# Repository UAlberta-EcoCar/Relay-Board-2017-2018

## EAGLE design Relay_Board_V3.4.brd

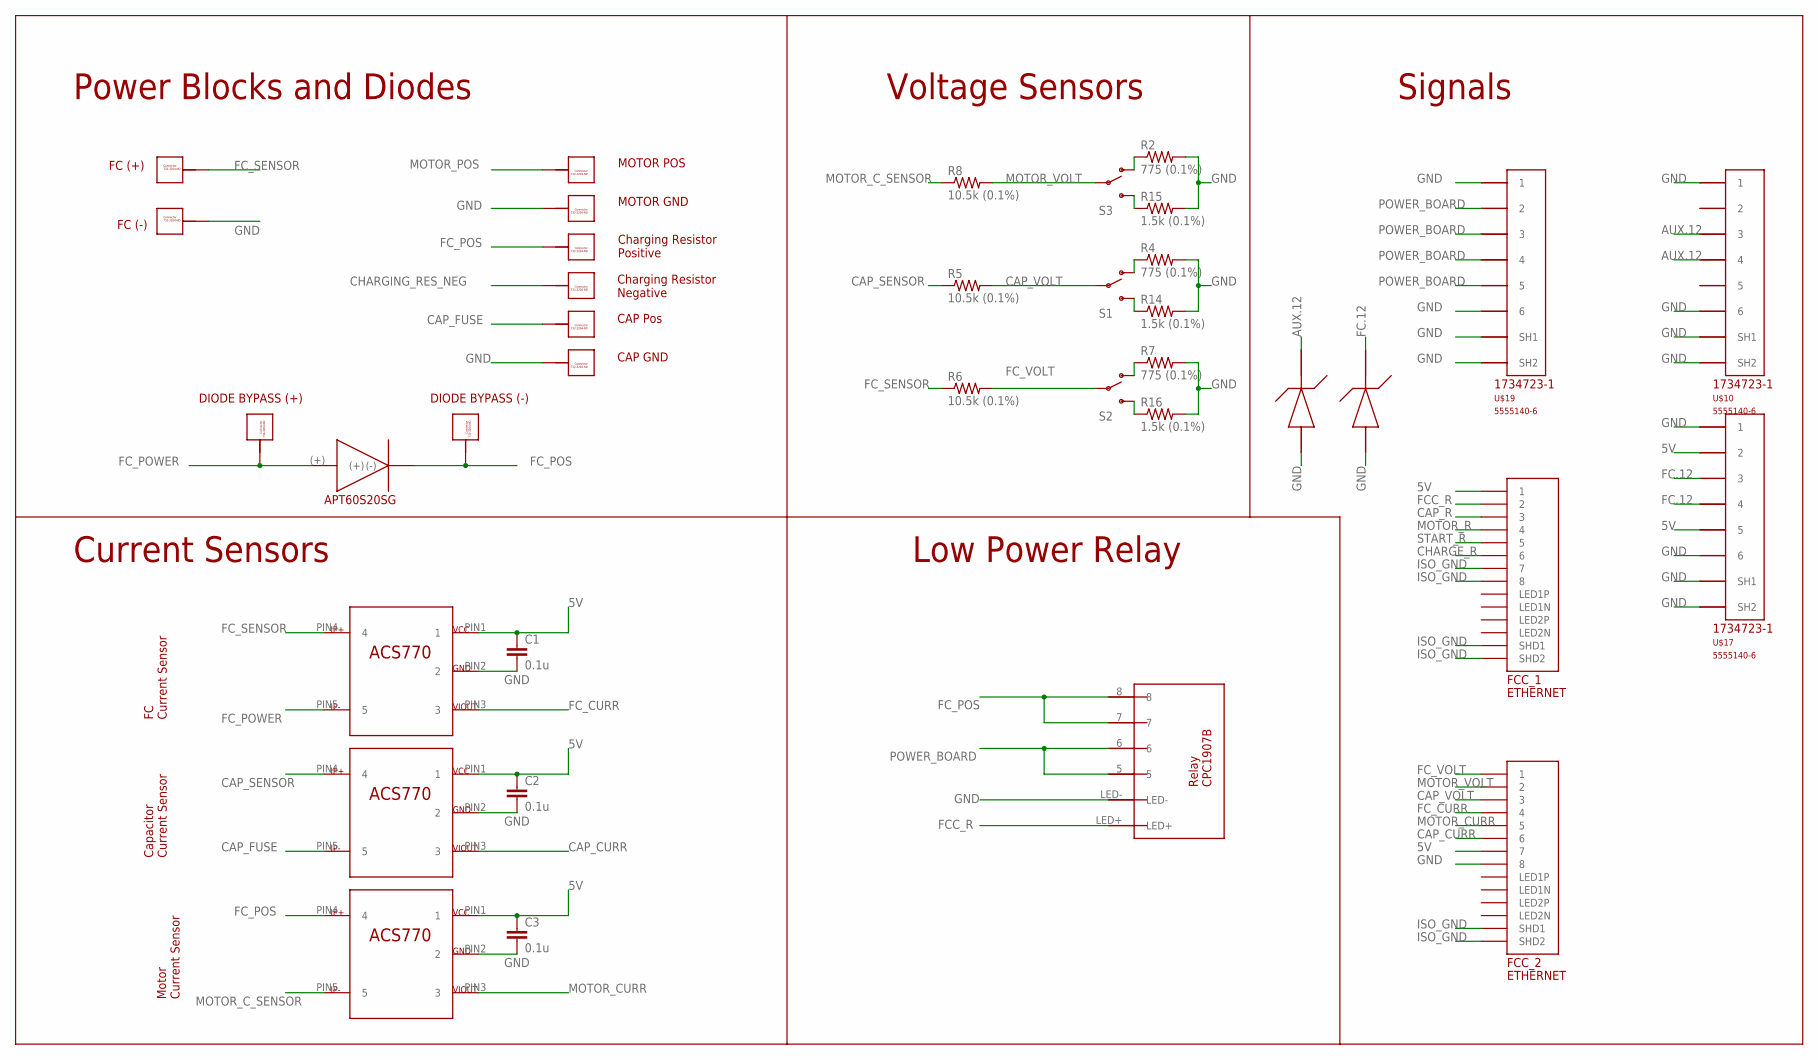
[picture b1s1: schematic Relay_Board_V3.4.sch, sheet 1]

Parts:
C1, C2, C3: 0.1u; 0603-CAP
CAP.GND, CAP.POS, CAP.POS1, CAP.POS2: 732-3204-ND_CONNECTOR; 732-3204-ND
D1: APT60S20SG; TO268
FC.GND, FC.POS: 732-3204-ND_CONNECTOR; 732-3204-ND
FCC_1, FCC_2: ETHERNET; A122645-ND
MOTOR.GROUND, MOTOR.POSITIVE: 732-3204-ND_CONNECTOR; 732-3204-ND
R2, R4, R7: 775 (0.1%); R0805
R5, R6, R8: 10.5k (0.1%); R0805
R14, R15, R16: 1.5k (0.1%); R0805
RES.NEG, RES.POS: 732-3204-ND_CONNECTOR; 732-3204-ND
S1, S2, S3: SWITCH-SPDTPTH; SWITCH-SPDT
U$7, U$8, U$9: ACS770LCB_CURRENTSENSOR
U$10, U$17, U$19: 5555140-6; 1734723-1_RJ11
U$15, U$16: P6KE15A-E3/54GICT-ND_TVS_DIODE
U$22: RELAY-CPC1907B

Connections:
5V: C1.1, C2.1, C3.1, FCC_1.P$1 (1), FCC_2.P$7 (7), U$7.PIN1 (1), U$8.PIN1 (1), U$9.PIN1 (1), U$17.2, U$17.5
AUX.12: U$10.3, U$10.4, U$16.P$2 (P(-)); also elsewhere on the board
CAP_CURR: FCC_2.P$6 (6), U$8.PIN3 (3)
CAP_FUSE: CAP.POS.P$1, CAP.POS.P$2, CAP.POS.P$3, CAP.POS.P$4, CAP.POS.P$5, CAP.POS.P$6, CAP.POS.P$7, CAP.POS.P$8, CAP.POS.P$9, CAP.POS.P$10, U$8.PIN5 (5)
CAP_R: FCC_1.P$3 (3); also elsewhere on the board
CAP_SENSOR: R5.1, U$8.PIN4 (4); also elsewhere on the board
CAP_VOLT: FCC_2.P$3 (3), R5.2, S1.2
CHARGE_R: FCC_1.P$6 (6); also elsewhere on the board
CHARGING_RES_NEG: RES.NEG.P$1, RES.NEG.P$2, RES.NEG.P$3, RES.NEG.P$4, RES.NEG.P$5, RES.NEG.P$6, RES.NEG.P$7, RES.NEG.P$8, RES.NEG.P$9, RES.NEG.P$10; also elsewhere on the board
FC.12: U$15.P$2 (P(-)), U$17.3, U$17.4; also elsewhere on the board
FCC_R: FCC_1.P$2 (2), U$22.LED+
FC_CURR: FCC_2.P$4 (4), U$7.PIN3 (3)
FC_POS: CAP.POS2.P$1, CAP.POS2.P$2, CAP.POS2.P$3, CAP.POS2.P$4, CAP.POS2.P$5, CAP.POS2.P$6, CAP.POS2.P$7, CAP.POS2.P$8, CAP.POS2.P$9, CAP.POS2.P$10, D1.(-), D1.C@1 ((-)), D1.C@2 ((-)), RES.POS.P$1, RES.POS.P$2, RES.POS.P$3, RES.POS.P$4, RES.POS.P$5, RES.POS.P$6, RES.POS.P$7, RES.POS.P$8, RES.POS.P$9, RES.POS.P$10, U$9.PIN4 (4), U$22.7, U$22.8; also elsewhere on the board
FC_POWER: CAP.POS1.P$1, CAP.POS1.P$2, CAP.POS1.P$3, CAP.POS1.P$4, CAP.POS1.P$5, CAP.POS1.P$6, CAP.POS1.P$7, CAP.POS1.P$8, CAP.POS1.P$9, CAP.POS1.P$10, D1.(+), U$7.PIN5 (5)
FC_SENSOR: FC.POS.P$1, FC.POS.P$2, FC.POS.P$3, FC.POS.P$4, FC.POS.P$5, FC.POS.P$6, FC.POS.P$7, FC.POS.P$8, FC.POS.P$9, FC.POS.P$10, R6.1, U$7.PIN4 (4)
FC_VOLT: FCC_2.P$1 (1), R6.2, S2.2
GND: C1.2, C2.2, C3.2, CAP.GND.P$1, CAP.GND.P$2, CAP.GND.P$3, CAP.GND.P$4, CAP.GND.P$5, CAP.GND.P$6, CAP.GND.P$7, CAP.GND.P$8, CAP.GND.P$9, CAP.GND.P$10, FC.GND.P$1, FC.GND.P$2, FC.GND.P$3, FC.GND.P$4, FC.GND.P$5, FC.GND.P$6, FC.GND.P$7, FC.GND.P$8, FC.GND.P$9, FC.GND.P$10, FCC_2.P$8 (8), MOTOR.GROUND.P$1, MOTOR.GROUND.P$2, MOTOR.GROUND.P$3, MOTOR.GROUND.P$4, MOTOR.GROUND.P$5, MOTOR.GROUND.P$6, MOTOR.GROUND.P$7, MOTOR.GROUND.P$8, MOTOR.GROUND.P$9, MOTOR.GROUND.P$10, R2.2, R4.2, R7.2, R14.2, R15.2, R16.2, U$7.PIN2 (2), U$8.PIN2 (2), U$9.PIN2 (2), U$10.1, U$10.6, U$10.SH1, U$10.SH2, U$15.P$1 (P(+)), U$16.P$1 (P(+)), U$17.1, U$17.6, U$17.SH1, U$17.SH2, U$19.1, U$19.6, U$19.SH1, U$19.SH2, U$22.LED-; also elsewhere on the board
ISO_GND: FCC_1.P$7 (7), FCC_1.P$8 (8), FCC_1.P$13 (SHD1), FCC_1.P$14 (SHD2), FCC_2.P$13 (SHD1), FCC_2.P$14 (SHD2); also elsewhere on the board
MOTOR_CURR: FCC_2.P$5 (5), U$9.PIN3 (3)
MOTOR_C_SENSOR: R8.1, U$9.PIN5 (5); also elsewhere on the board
MOTOR_POS: MOTOR.POSITIVE.P$1, MOTOR.POSITIVE.P$2, MOTOR.POSITIVE.P$3, MOTOR.POSITIVE.P$4, MOTOR.POSITIVE.P$5, MOTOR.POSITIVE.P$6, MOTOR.POSITIVE.P$7, MOTOR.POSITIVE.P$8, MOTOR.POSITIVE.P$9, MOTOR.POSITIVE.P$10; also elsewhere on the board
MOTOR_R: FCC_1.P$4 (4); also elsewhere on the board
MOTOR_VOLT: FCC_2.P$2 (2), R8.2, S3.2
unnamed: R4.1, S1.1 (O)
unnamed: R14.1, S1.3 (S)
unnamed: R2.1, S3.1 (O)
unnamed: R15.1, S3.3 (S)
unnamed: R7.1, S2.1 (O)
unnamed: R16.1, S2.3 (S)
POWER_BOARD: U$19.2, U$19.3, U$19.4, U$19.5, U$22.5, U$22.6
START_R: FCC_1.P$5 (5); also elsewhere on the board

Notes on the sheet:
FC Current Sensor
Charging Resistor Positive
Charging Resistor Negative
Motor Current Sensor
FC (+)
FC (-)
Voltage Sensors
Power Blocks and Diodes
Signals
DIODE BYPASS (+)
DIODE BYPASS (-)
Current Sensors
Capacitor Current Sensor
CAP Pos
CAP GND
MOTOR GND
MOTOR POS
Low Power Relay

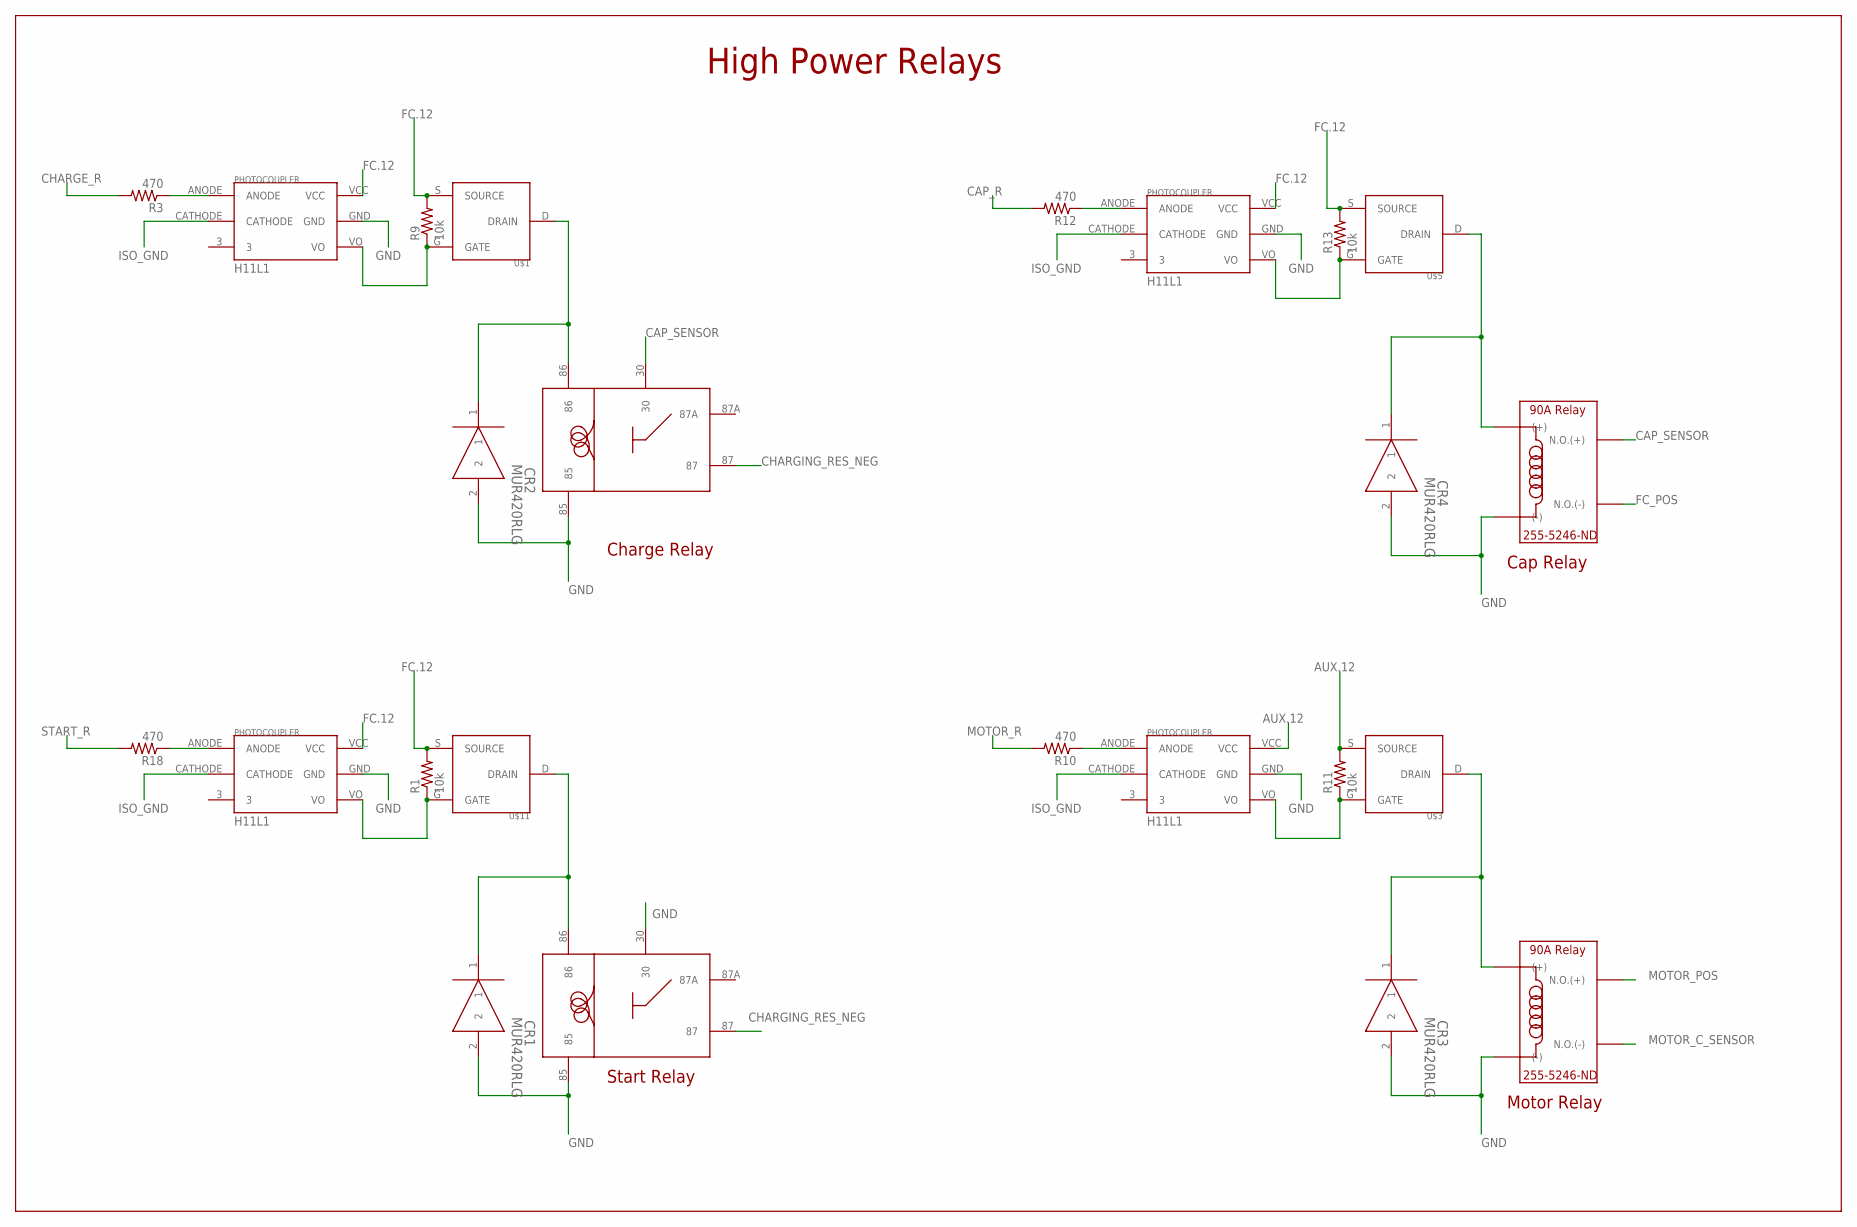
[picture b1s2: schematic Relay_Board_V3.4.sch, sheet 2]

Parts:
CR1, CR2, CR3, CR4: MUR420RLG; DO-201AD
R1, R9, R11, R13: 10k; 0603-RES
R3, R10, R12, R18: 470; 0603-RES
START.RELAY1, START.RELAY2: VCF4-1000
U$1, U$3, U$5, U$11: DMP3056L-7DMP3056L-7; DMP3056L-7
U$2, U$4, U$6, U$12: H11L1H11L1; H11L1
U$13, U$14: 255-5246-ND

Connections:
AUX.12: R11.2, U$3.S (SOURCE), U$4.VCC; also elsewhere on the board
CAP_R: R12.2; also elsewhere on the board
CAP_SENSOR: START.RELAY2.30, U$13.NO(+) (N.O.(+)), U$13.NO(++) (N.O.(+)); also elsewhere on the board
CHARGE_R: R3.2; also elsewhere on the board
CHARGING_RES_NEG: START.RELAY1.87, START.RELAY2.87; also elsewhere on the board
FC.12: R1.2, R9.2, R13.2, U$1.S (SOURCE), U$2.VCC, U$5.S (SOURCE), U$6.VCC, U$11.S (SOURCE), U$12.VCC; also elsewhere on the board
FC_POS: U$13.NO(-) (N.O.(-)), U$13.NO(--) (N.O.(-)); also elsewhere on the board
GND: CR1.2, CR2.2, CR3.2, CR4.2, START.RELAY1.30, START.RELAY1.85, START.RELAY2.85, U$2.GND, U$4.GND, U$6.GND, U$12.GND, U$13.(-), U$13.(--) ((-)), U$14.(-), U$14.(--) ((-)); also elsewhere on the board
ISO_GND: U$2.CATHODE, U$4.CATHODE, U$6.CATHODE, U$12.CATHODE; also elsewhere on the board
MOTOR_C_SENSOR: U$14.NO(-) (N.O.(-)), U$14.NO(--) (N.O.(-)); also elsewhere on the board
MOTOR_POS: U$14.NO(+) (N.O.(+)), U$14.NO(++) (N.O.(+)); also elsewhere on the board
MOTOR_R: R10.2; also elsewhere on the board
unnamed: R9.1, U$1.G (GATE), U$2.VO
unnamed: R3.1, U$2.ANODE
unnamed: CR2.1, START.RELAY2.86, U$1.D (DRAIN)
unnamed: R11.1, U$3.G (GATE), U$4.VO
unnamed: R10.1, U$4.ANODE
unnamed: CR3.1, U$3.D (DRAIN), U$14.(+), U$14.(++) ((+))
unnamed: R13.1, U$5.G (GATE), U$6.VO
unnamed: R12.1, U$6.ANODE
unnamed: CR4.1, U$5.D (DRAIN), U$13.(+), U$13.(++) ((+))
unnamed: R1.1, U$11.G (GATE), U$12.VO
unnamed: R18.1, U$12.ANODE
unnamed: CR1.1, START.RELAY1.86, U$11.D (DRAIN)
START_R: R18.2; also elsewhere on the board

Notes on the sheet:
Start Relay
Charge Relay
High Power Relays
Motor Relay
Cap Relay

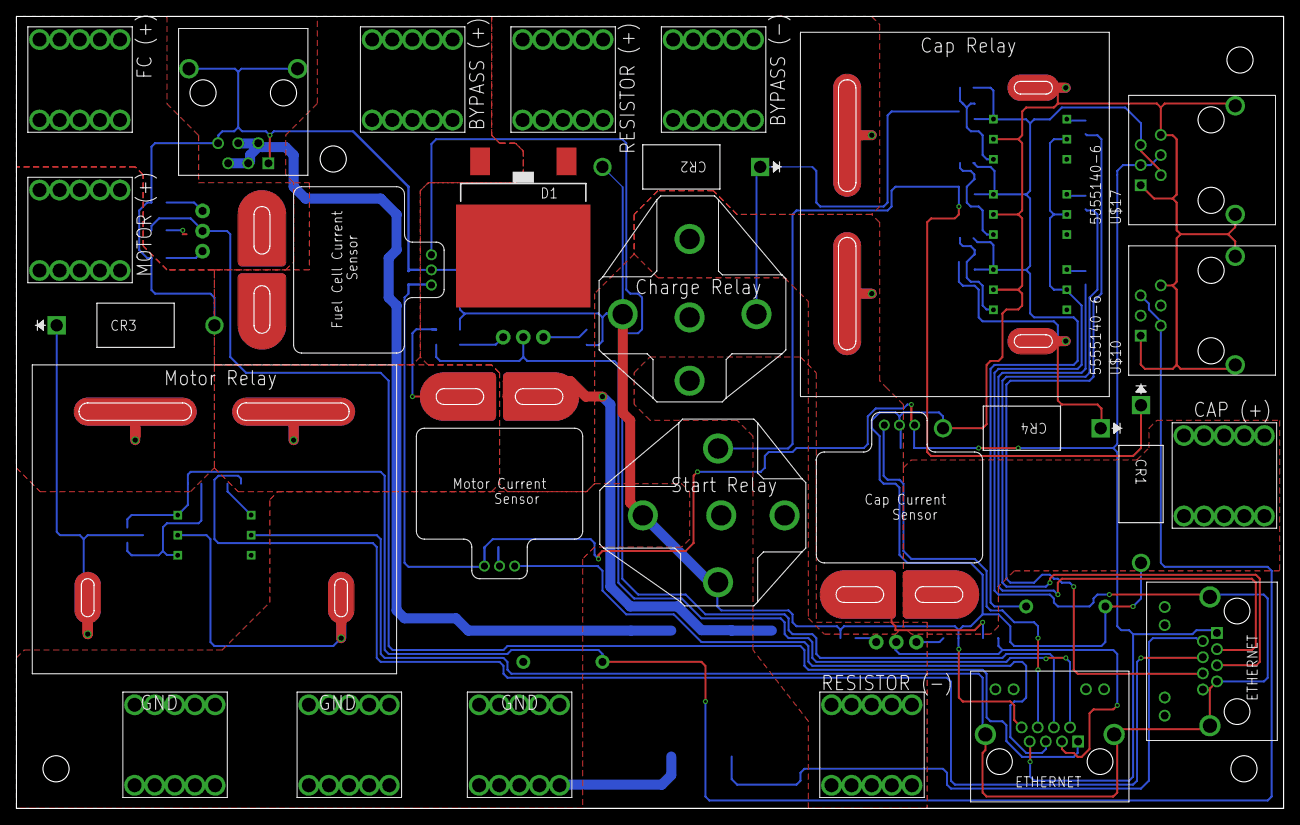
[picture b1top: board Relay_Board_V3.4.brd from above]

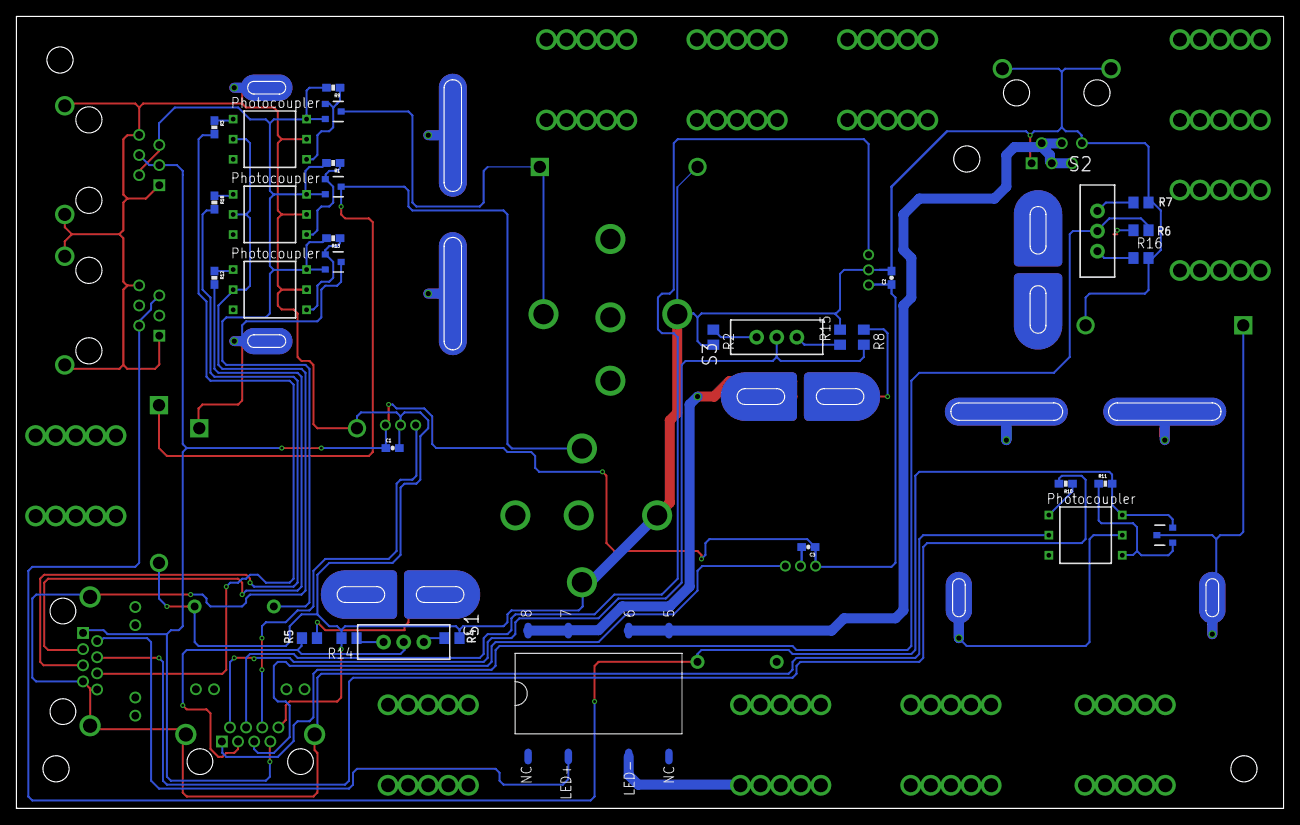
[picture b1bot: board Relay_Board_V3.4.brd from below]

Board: 2 copper layers, 160.0 x 100.0 mm, 65 parts (32 on the bottom side), 43 nets.

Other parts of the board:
U$18, U$20, U$21, U$23: STAND-OFF

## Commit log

2017-10-21 Relay Board V3 added
2017-10-28 Schematic Complete
2017-11-04 Major Trace Routes
2017-11-13 Board Routed
2017-12-01 Board Complete for 2017
2017-12-02 Updated OptoIsolator Part so it is same as FCC
2017-12-02 Added Labels to Ethernet connectors
2017-12-02 Added RJ-11
2017-12-02 Schematic Fix
2017-12-05 Gerbers Generated
2018-01-17 Fixed RJ-11 and thermals
2018-01-20 Fixed Traced Separation
2018-01-21 Added Parts List

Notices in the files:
parts and their libraries:
SparkFun-Passives: Licensing: Creative Commons ShareAlike 4.0 International - https://creativecommons.org/licenses/by-sa/4.0
